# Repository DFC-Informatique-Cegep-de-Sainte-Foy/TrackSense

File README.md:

# TrackSense 

> Le projet TrackSense est développé par des étudiants du programme [Techniques de l'informatique - Programmation, bases de données et serveurs - DEC accéléré](https://dfc.csfoy.ca/retourner-aux-etudes/programmes-a-temps-plein/informatique/techniques-de-linformatique-programmation-bases-de-donnees-et-serveurs-dec-accelere/) du cégep de Ste-Foy, dans le cadre de leur projet de synthèse.

> - TrackSense est un boitier à fixer sur votre vélo pour enregistrer vos trajets.
> - L'application mobile permet la récupération, l'affichage et la sauvegarde des trajets. Elle sert également à la configuration du TrackSense.
> - L'API (serveur Web) est l'interface permettant de sauvegarder et récupérer les trajets.
> - La base de données sert à sauvegarder les données.

> Le présent dépôt rassemble les informations générales et tout ce qui n'est pas du développement des applications (embarquée, mobile, Web, Base de données). Chaque application à son dépôt.

## Créer votre TrackSense !

> Pour garantir le bon fonctionnement de votre TrackSense, de sa communication avec votre application mobile et la sauvegarde de vos données, veuillez suivre les étapes [disponibles ici](https://github.com/DFC-Informatique-Cegep-de-Sainte-Foy/TrackSense/wiki) !

## Application embarquée

> L'application embarquée est le programme qui va s'exécuter à l'intérieur de votre TrackSense.
> Vous trouverez son dépôt GitHub [ici](https://github.com/DFC-Informatique-Cegep-de-Sainte-Foy/420-W57-SF_TrackSense_AppEmbarque).

## Application mobile

> L'application mobile est nécessaire pour configurer et communiquer avec votre TrackSense.
> Vous trouverez son dépôt GitHub [ici](https://github.com/DFC-Informatique-Cegep-de-Sainte-Foy/420-W57-SF_TrackSense_AppMobile).

## Application Web (API)

> L'application Web est l'interface qui vous permet de communiquer avec votre base de données. Elle peut être hébergée en ligne ou chez vous.
> Vous trouverez son dépôt GitHub [ici](https://github.com/DFC-Informatique-Cegep-de-Sainte-Foy/420-W57-SF_TrackSense_ServeurWeb).

## Base de données

> La base de données est l'endroit où sont stockées vos données. Elle n'est accessible que via l'application Web.
> Vous trouverez son dépôt GitHub [ici](https://github.com/DFC-Informatique-Cegep-de-Sainte-Foy/420-W57-SF_TrackSense_BD).

## Manuel utilisateur

> Comment utiliser mon TrackSense ? Quelles sont les fonctionnalités ? Ça fait quoi quand j'appuie sur un bouton ?
> Pour avoir toutes les réponses à ces questions et bien d'autres, vous trouverez le manuel de l'utilisateur [ici](https://github.com/DFC-Informatique-Cegep-de-Sainte-Foy/TrackSense/wiki/Manuel) !  

## Informations générales

> Quelques informations et/ou éléments supplémentaires :
> - [Logo](./TrackSense/tree/main/Logo/)
> - [Composants](./TrackSense/tree/main/Composants)

## Contributeurs

### Session hiver 2024

>-  [David Fournel-Vézina](https://github.com/DavidFV2296190)
>-  [Rémi St-Pierre](https://github.com/ray3331)
>-  [Changfeng Zhao](https://github.com/Kuma-Lingxi)

### Session été 2023

>-  [Dominique Lebrun](https://github.com/dodo-12-37)
>-  [Loïc Delas](https://github.com/LoicDelas)
>-  [Tien Binh Nguyen](https://github.com/binhnguyen84)
>-  [Simon Quillaud](https://github.com/simonquillaud)

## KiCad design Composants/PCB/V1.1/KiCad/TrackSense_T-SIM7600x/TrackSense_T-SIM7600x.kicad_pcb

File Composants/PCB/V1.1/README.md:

# Tracksense PCB V1.1
## Design
Cette nouvelle plaquette est compatible avec le LilyGo T-SIM7600x. Tous les fichiers produits avec [KiCad V8.0.0](https://gitlab.com/kicad) sont placés sous le répertoire KiCad. Il est possible de faire fabriquer cette plaquette chez de multiples fournisseurs. Pour simplifier le processus de fabrication de la plaquette, le répertoire [*Kicad/TrackSense-T-SIM7600x/Production*](\KiCad\TrackSense_T-SIM7600x\production) contient une archive ZIP qui peut être directement téléversé sur le site de [JLCPCB](https://jlcpcb.com). Cette archive a été construite à l'aide de l'extension KiCad [Fabrication Toolkit](https://github.com/bennymeg/Fabrication-Toolkit) qui permet de produire les fichiers Gerber ainsi qu'une nomenclature (*bill of materials*). Il est donc ainsi possible de faire assembler la plaquette et d'y faire installer le connecteurs par le fabricant. (*Toutes les composantes peuvent être facilement soudées à la main pour réduire les coûts*)

### Vue du dessus

### Vue du dessous

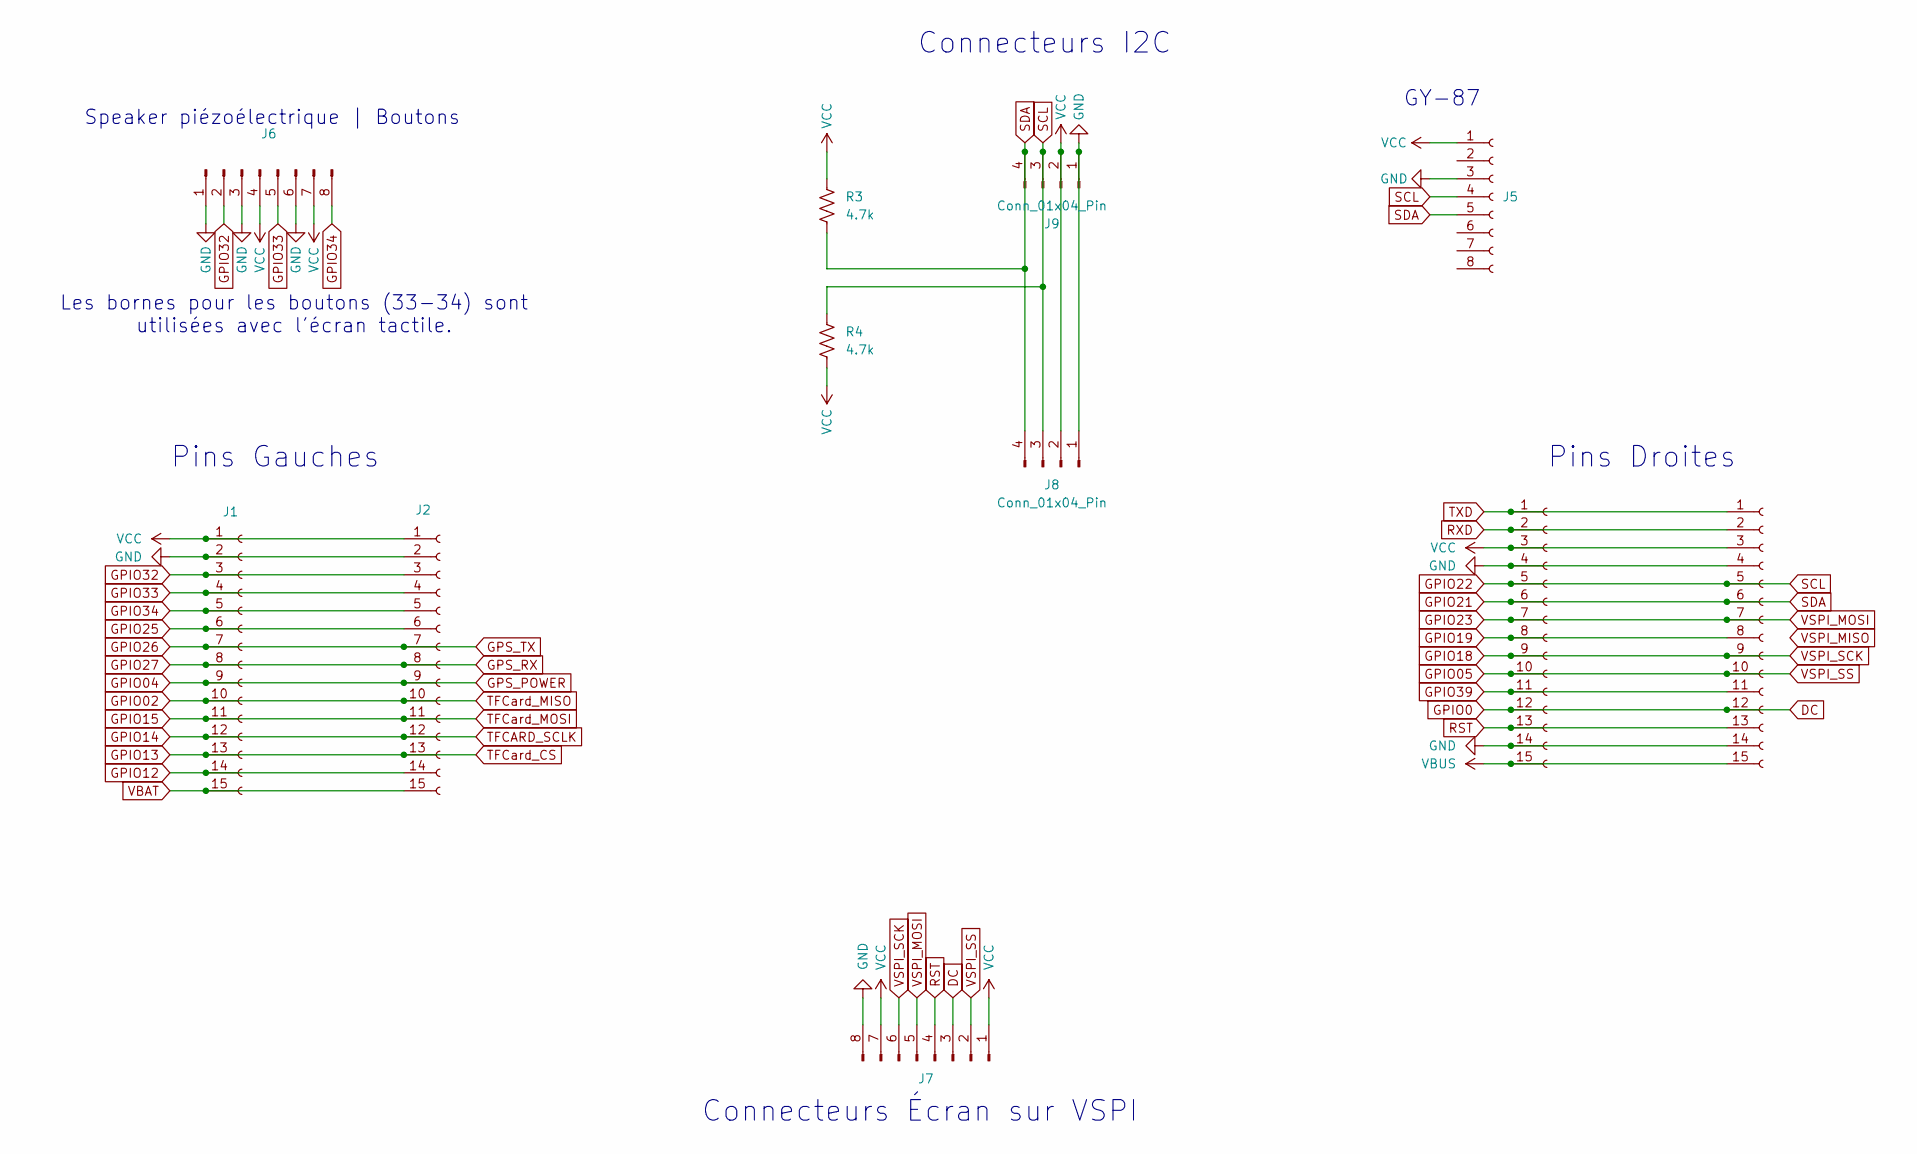
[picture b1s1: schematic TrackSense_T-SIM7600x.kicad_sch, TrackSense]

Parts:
J1, J2, J3, J4: Conn_01x15_Socket; PinSocket_1x15_P2.54mm_Vertical
J5: Conn_01x08_Socket; PinSocket_1x08_P2.54mm_Vertical
J6, J7: Conn_01x08_Pin; JST_XH_S8B-XH-A-1_1x08_P2.50mm_Horizontal
J8, J9: Conn_01x04_Pin; JST_XH_S4B-XH-A-1_1x04_P2.50mm_Horizontal
R3, R4: 4.7k; R_Axial_DIN0207_L6.3mm_D2.5mm_P10.16mm_Horizontal

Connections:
DC: J3.12, J4.12, J7.3
GND: J1.2, J2.2, J3.4, J3.14, J4.4, J4.14, J5.3, J6.1, J6.3, J6.6, J7.8, J8.1, J9.1
GPIO02: J1.10, J2.10
GPIO04: J1.9, J2.9
GPIO05: J3.10, J4.10, J7.2
GPIO12: J1.14, J2.14
GPIO13: J1.13, J2.13
GPIO14: J1.12, J2.12
GPIO15: J1.11, J2.11
GPIO18: J3.9, J4.9, J7.6
GPIO19: J3.8, J4.8
GPIO21: J3.6, J4.6, J5.5, J8.4, J9.4, R3.2
GPIO22: J3.5, J4.5, J5.4, J8.3, J9.3, R4.2
GPIO23: J3.7, J4.7, J7.5
GPIO25: J1.6, J2.6
GPIO26: J1.7, J2.7
GPIO27: J1.8, J2.8
GPIO32: J1.3, J2.3, J6.2
GPIO33: J1.4, J2.4, J6.5
GPIO34: J1.5, J2.5, J6.8
GPIO39: J3.11, J4.11
RST: J3.13, J4.13, J7.4
RXD: J3.2, J4.2
TXD: J3.1, J4.1
VBAT: J1.15, J2.15
VBUS: J3.15, J4.15
VCC: J1.1, J2.1, J3.3, J4.3, J5.1, J6.4, J6.7, J7.1, J7.7, J8.2, J9.2, R3.1, R4.1

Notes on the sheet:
Pins Droites
Connecteurs I2C
Les bornes pour les boutons (33-34) sont utilisées avec l'écran tactile.
GY-87
Pins Gauches
Connecteurs Écran sur VSPI
Speaker piézoélectrique | Boutons

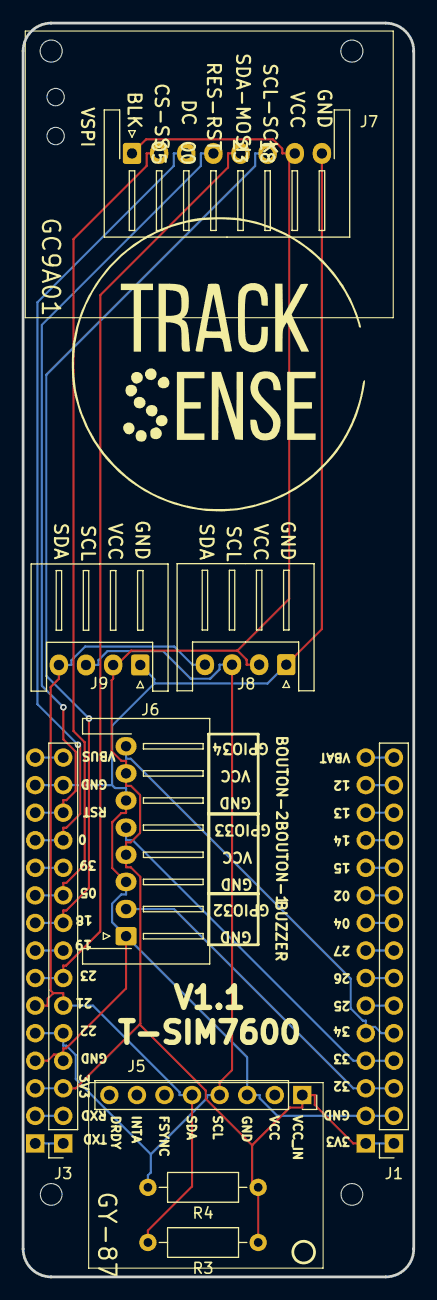
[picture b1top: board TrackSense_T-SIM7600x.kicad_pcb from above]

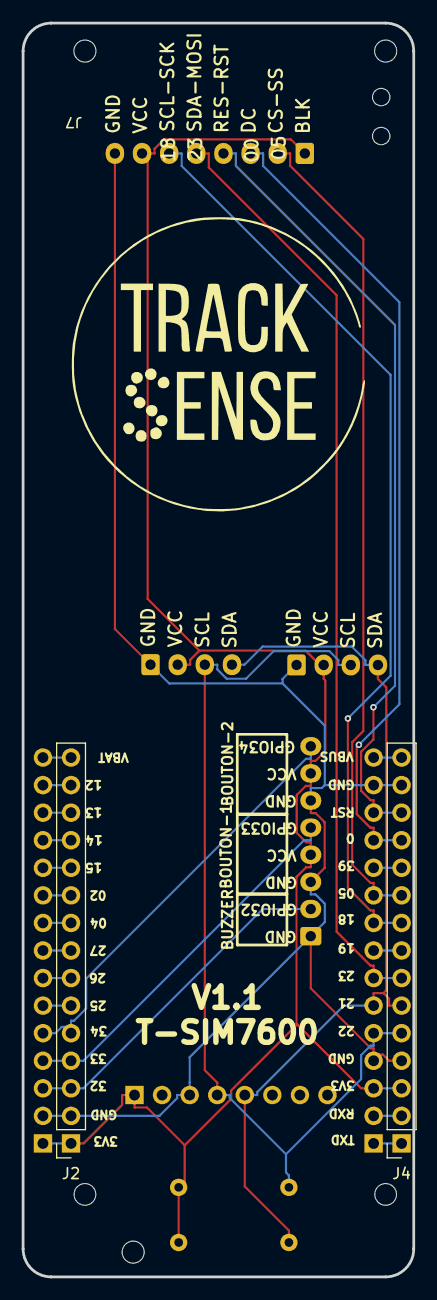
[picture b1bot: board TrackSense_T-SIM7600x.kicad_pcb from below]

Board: 2 copper layers, 36.0 x 115.5 mm, 20 parts (3 on the bottom side), 27 nets.

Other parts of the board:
G1, G2: LOGO; TS_LOGO_FOOTPRINT
Hole_gge6255: Hole_gge6255
Hole_gge6258: Hole_gge6258
Hole_gge12314: Hole_gge12314
Hole_gge26318: Hole_gge26318
Hole_gge26333: Hole_gge26333
Hole_gge31514: Hole_gge31514
Hole_gge31529: Hole_gge31529

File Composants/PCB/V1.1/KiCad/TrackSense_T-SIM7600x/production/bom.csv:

Designator,Footprint,Quantity,Value,LCSC Part #
Hole_gge12314,Hole_gge12314,1,Hole_gge12314,
Hole_gge26318,Hole_gge26318,1,Hole_gge26318,
Hole_gge26333,Hole_gge26333,1,Hole_gge26333,
Hole_gge31514,Hole_gge31514,1,Hole_gge31514,
Hole_gge31529,Hole_gge31529,1,Hole_gge31529,
Hole_gge6255,Hole_gge6255,1,Hole_gge6255,
Hole_gge6258,Hole_gge6258,1,Hole_gge6258,
"J1, J2, J3, J4",PinSocket_1x15_P2.54mm_Vertical,4,Conn_01x15_Socket,
J5,PinSocket_1x08_P2.54mm_Vertical,1,Conn_01x08_Socket,
"J6, J7",JST_XH_S8B-XH-A-1_1x08_P2.50mm_Horizontal,2,Conn_01x08_Pin,
"J8, J9",JST_XH_S4B-XH-A_1x04_P2.50mm_Horizontal,2,Conn_01x04_Pin,
"R3, R4",R_Axial_DIN0207_L6.3mm_D2.5mm_P10.16mm_Horizontal,2,4.7k,

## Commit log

2024-05-28 add gitignore
2024-05-28 update gitignore
2024-05-28 Nouveaux contributeurs
2024-05-28 PCB V1.1 T-SIM7600x
2024-05-30 correction .gitignore
2024-06-04 nouveaux liens
